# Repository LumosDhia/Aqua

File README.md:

# Aqua: smart farm water assistant

Hackathon project for Kizuna 2026 (21 to 22 November 2026, Esprit Bloc E, teams of 2 to 4, prizes 4000 / 2000 / 1000 TND). Theme: water, energy and food. Target users: Tunisian farmers.

Source material from the 20 November sessions:

- Ideas, software plan, roadmap, checklist, walkthrough website: `~/our idea/`
- Working scaffold (backend, frontend, firmware, compose): `~/our idea/project/`
- Desktop and Android wrappers: `~/our idea/app/`
- Hardware step by step PDF with wiring and ESP32 code: `~/smart-watering-guide.pdf`
- Hackathon site copy: `~/kizuna2026/`

## 1. What the project should be

A farm assistant that knows the soil, the weather and the crop, and decides when and how much to water.

Core logic (the heart of the demo):

| Situation | Action |
|---|---|
| Tank empty | Block the pump, raise an alarm |
| Soil dry and rain is forecast | Skip watering, count the water saved |
| Soil dry and no rain | Short pump dose |
| Soil very dry | Tiny emergency dose |

Feature groups, by priority:

- Must: soil and tank sensors with a live dashboard, rain-aware decision, crop dropdown (popular Tunisian crops) with per-crop water calculation, water saved counter.
- Should: water budget calculator (week, month, year, per source: SONEDE, well, rain tank), WhatsApp alerts, chatbot specialised in Tunisian farming (Derja, French, English, with voice), farm visualiser with coloured plots.
- Could: solar panel calculator, season changing UI (the interface changes with the season).
- Maybe: satellite NDVI map, heat and drought warning, planting advisor, pest and fertiliser calendar, leak detection, weekly PDF report, offline mode, cooperative multi-farm view.
- Later: neighbour water market (premium, needs a legal check, show as a mock screen).

Extra software adds that need no hardware: photo plant doctor, WhatsApp as the main interface, weekly smart schedule with a reason per decision, litres and dinars saved counter, simulation sliders, demo data generator.

Accessibility: the farmer can talk to the chatbot with voice.

## 2. Architecture and stack

| Layer | Choice |
|---|---|
| Frontend | React, Vite, TypeScript, Tailwind, Recharts, Leaflet, i18next with RTL |
| Backend | FastAPI (Python), SQLAlchemy |
| Database | PostgreSQL in Docker on the VPS (SQLite in dev) |
| Sensors | ESP32 posts over HTTP every 15 minutes |
| Live updates | WebSocket or SSE from FastAPI |
| Weather | Open-Meteo (free, no key) |
| Chatbot | Open model served on our GPU server (gpu.mavubo.com) through an OpenAI compatible API, with vision for the plant doctor |
| Voice | Whisper for speech to text |
| WhatsApp | Twilio sandbox for the demo, Meta Cloud API later |
| Deploy | Docker Compose on the VPS behind Nginx Proxy Manager with https |
| Auth | JWT |
| Apps | Electron (desktop), Capacitor (Android) |

Rules: the apps always talk to the API, never directly to the database. Do not use Next.js, Flutter or React Native.

Hardware (from the owned inventory): ESP32, capacitive soil moisture sensor V1.2, HC-SR04 ultrasonic sensor for tank level (ECHO through a divider of 2 x 1k ohm), water sensor module as rain detector, 5V relay, mini DC water pump with its own power supply, LEDs with 330 ohm resistors, buzzer. The Arduino Uno is not used because it has no Wi-Fi. Still needed: silicone tube, a tank, a breadboard and wires.

Repo layout:

```
backend/    FastAPI + SQLAlchemy + Alembic
frontend/   React + Vite
firmware/   ESP32 sketch
docker-compose.yml   api + postgres
```

## 3. Folders and how to run it

```
site/      product home page (static, open index.html)
backend/   FastAPI API with login and roles
web/       login page and dashboard (React, Vite, TypeScript, Tailwind, Lucide)
firmware/  ESP32 sketch
design/    reference images the pages follow
```

Run the dashboard locally:

```
cd backend && python3 -m venv .venv && .venv/bin/pip install -r requirements.txt
.venv/bin/python seed.py && .venv/bin/uvicorn app.main:app --port 8000
cd web && npm install && npm run dev        # http://127.0.0.1:5173
```

The dashboard draws the farm from the plots the farmer enters: each plot gets a share of the map proportional to its area, and plots with a warning (dry soil, low tank, waiting for rain) get a glowing marker and a note on the plot.

### AI models on the GPU server

All AI features (the chat advisor, reading CVs, reading farm drawings, the plant doctor) call a language model hosted on our GPU server, `gpu.mavubo.com`, through an OpenAI compatible API (`POST /v1/chat/completions` with a JSON schema for structured answers). The backend settings are:

```
LLM_API_URL=https://gpu.mavubo.com/v1
LLM_API_KEY=            # only if the server asks for a key
LLM_MODEL=qwen2.5vl:7b  # the model name exactly as the server lists it
```

Serve the models with Ollama (simplest) or vLLM. Models to download on the GPU server:

| Use | Model | Pull command (Ollama) | VRAM, about |
|---|---|---|---|
| Default: chat, CVs, drawings, plant photos (text and images) | Qwen2.5-VL 7B Instruct | `ollama pull qwen2.5vl:7b` | 8 GB |
| Better quality, same features, if the GPU has room | Qwen2.5-VL 32B Instruct | `ollama pull qwen2.5vl:32b` | 24 GB |
| Text only, small GPU | Llama 3.1 8B Instruct | `ollama pull llama3.1:8b` | 6 GB |
| Text only, stronger reasoning | Qwen2.5 14B Instruct | `ollama pull qwen2.5:14b` | 10 GB |
| Speech to text for voice messages | Whisper large-v3 | `ollama` does not run it, use `faster-whisper` | 4 GB |

If you use vLLM instead, start it with the Hugging Face name, for example `vllm serve Qwen/Qwen2.5-VL-7B-Instruct`, and put that same name in `LLM_MODEL`. The chat advisor needs a model that can follow a JSON schema; the photo and drawing features need one of the vision models. Without the server the chat shows "The AI helper is not switched on yet" and everything else keeps working. The advisor sees the farm's live plots, readings and forecast, and accepts photos, PDFs and text files (up to four files of 5 MB per message). A long answer can take about 20 seconds.

### Workers

The Workers icon (under the chat in the left rail) holds the farm's team and its tasks. Add a worker, then assign tasks from the Tasks tab or from the chat: ask the advisor to check what needs doing and it proposes tasks as cards, and you approve each one (or Send all). The advisor never creates tasks on its own, so a photo or file in the chat cannot assign work. Managers and owners add and remove workers, technicians and above assign tasks and mark them done, viewers only read.

## Water, weather, market and jobs

The left rail has these pages (full plan in `docs/ROADMAP-water-market.md`):

- **Water**: tabs My water (tanks, wells, boreholes, the public network, with levels and refill per day), Needs (how much water the crops and animals need, from the FAO-56 method with the forecast evapotranspiration, the soil type and the irrigation efficiency, for today, 7 days, 30 days and a year, against what the farm has, with a plain verdict such as "You will run short in about 3 days") and Animals (herds and their drinking water).
- **Weather**: current conditions, 48 hours, 7 days, farm alerts (heat, frost, wind, heavy rain). Data comes from Open-Meteo, which needs no key. Its free tier is for non-commercial use, so check their terms or buy their plan before Aqua is sold.
- **Water market**: farmers list surplus water with photos, price (fixed, free or to agree), pickup or delivery, location and dates. Other farmers browse by governorate, source, price and distance, and send an inquiry. Sellers read and answer inquiries in their inbox.
- **Jobs**: farmers post a one-off task, a job for a period or a long-term job; anyone with an account applies; the farm accepts or declines. A job fills when enough people are accepted.

### People: accounts, hiring and trust

Two kinds of people use Aqua. At sign-up you choose **farmer** or **farm worker**, and one person can switch sides later without losing anything.

- **Farmers** get a setup wizard (name and region, crops and sizes, water sources, animals, a written description or a hand-drawn picture), then a dashboard built from the answers.
- **Workers** get a Worker home (active work, applications, jobs near them, messages, profile checklist), a profile (headline, skills, languages, where they live, how far they will travel, public or private) and a CV that they can upload, fill in by hand or describe in words. Reading and writing CVs with AI needs the AI model server; without it the manual form still works.
- **Matching by distance**: workers see jobs within their own travel distance and within the reach the farm gave the job. Farmers see public workers who are looking for work within the radius they pick. Private profiles never appear and cannot apply.
- **Hiring**: accepting an application creates an engagement. The farmer marks it finished (it becomes confirmed work history on the worker's public profile), disapproves it with a reason, or offers full time after temporary work.
- **Chat**: after a hire, the farm and the worker talk in the Messages page, with unread counts. Email and phone are never shown.
- **Reports**: anyone can report a person (scam, no-show, unsafe, harassment, other), at most five a day. An admin reviews them, adds a note, resolves or dismisses, and can suspend an account, which locks it out at once and can be lifted.

CV files and farm drawings are private files, served only to their owner (and farm members for drawings). People and farms are placed by governorate, so distances are between governorate centres.

### Sample community

`backend/seed_market.py` creates eight fictional farmers (farms, water, listings with photos, job posts, inquiries and applications) so the market and jobs pages look real. Everyone shares the password in the script (`aqua-demo-2026`), for example `mohamed.karoui@aqua.test`. All people and businesses are invented. Photos are from Wikimedia Commons, credits in `backend/seed_media/CREDITS.md`.

```
cd backend
.venv/bin/python seed.py            # demo farm and the five role logins
.venv/bin/python seed_market.py     # sample community (add --reset to start over)
```

`backend/seed_people.py` adds eight fictional workers (profiles and CVs, one private, one not looking), three hires (active, finished, disapproved) with chats and two reports. It needs the two scripts above first, and `--reset` removes only the people it made.

```
.venv/bin/python seed_people.py     # sample workers, hires, chats and reports
```

Delete the demo accounts before any real use.

### Deploying these changes

- The API creates the new tables and adds the plot `soil_type` column by itself on start.
- Uploaded photos live in the `uploads` volume in `docker-compose.yml` (`UPLOADS_DIR=/data/uploads`) and are served at `/uploads`. Proxy `/uploads` to the API together with `/api`.
- The sample community is for demos only, do not run `seed_market.py` or `seed_people.py` on a real farm database.

## 3b. Older notes on running the scaffold

### Run locally

```
# backend, terminal 1
cd ~/our\ idea/project/backend
python3 -m venv .venv && .venv/bin/pip install -r requirements.txt
.venv/bin/python seed.py
.venv/bin/uvicorn app.main:app --reload        # http://localhost:8000/docs

# frontend, terminal 2
cd ~/our\ idea/project/frontend
npm install && npm run dev                     # http://localhost:5173
```

### Deploy on the VPS

```
cp .env.example .env        # set POSTGRES_PASSWORD and DEVICE_API_KEY
docker compose up -d --build
```

The API binds to 127.0.0.1:8000. Put it behind Nginx Proxy Manager with https, then set `CORS_ORIGINS` to the real origins: `http://localhost`, `https://localhost`, `capacitor://localhost`, and `null` for Electron.

### Desktop and Android apps

```
cd ~/our\ idea/project
./link-wrappers.sh https://api.yourdomain.com
cd ../app
npm run desktop           # Electron
npm run android:build     # APK, needs the Android SDK
```

Android SDK install was still downloading at the end of the 20 November session. Check `ANDROID_HOME` before building. iOS needs a Mac.

### Firmware

Open `firmware/` in the Arduino IDE, set Wi-Fi name and password, the API URL and `DEVICE_API_KEY`. Calibrate the soil and tank values yourself, the numbers in the sketch are guesses. Power the pump from its own supply, not USB.

### API

- `GET /health`
- `GET /api/crops`, `GET/POST /api/farms`, `POST /api/farms/{id}/plots`
- `POST /api/readings` (header `X-API-Key`), `GET /api/plots/{id}/readings`
- `POST /api/plots/{id}/decide`, `GET /api/plots/{id}/saved`

## 4. Plan for the 25 hours

1. Hours 0 to 3: agree scope, split roles, collect crop data (Kc, water needs).
2. Hours 3 to 10: ESP32 prototype and backend receiving data, dashboard skeleton in parallel.
3. Hours 10 to 16: decision engine with weather API, crop calculator, water saved counter.
4. Hours 16 to 20: chatbot with voice, WhatsApp alert, farm visualiser.
5. Hours 20 to 23: polish, season theme, mock screens for market and solar.
6. Hours 23 to 25: rehearse the pitch, record a backup demo video.

Roles: hardware and sensors, backend and decision engine, frontend and visualiser, chatbot and pitch.

## 5. Done and not done

Done: scaffold with farms, plots, readings, rain-aware decision with live Open-Meteo, saved counter, seed data, 3 passing tests, dashboard with chart, ESP32 sketch, Compose tested with Postgres, Electron tested, Capacitor Android platform added.

Also done: login (JWT) and role based access control (admin, owner, manager, technician, viewer), see `~/our idea/project/README.md`.

Not done: FAO water formula (placeholder of 4 L/m2 now), chatbot, WhatsApp, Leaflet map, i18n, Android SDK finish.

## 6. Pitch outline

1. Problem: summer 2026 was the hottest on record in Tunisia, power cuts stop pumps, farmers lose water.
2. Idea: an assistant that knows soil, weather and crop.
3. Live demo: dry soil, rain forecast, the system saves water and tells the farmer on WhatsApp.
4. Impact: litres and dinars saved.
5. Growth: neighbour water market and cooperatives.
6. Why us: Tunisia and Japan, two cultures that farm with scarce water.

Risks: water resale rules in Tunisia, WhatsApp API approval time, Derja speech to text quality, sensor calibration. Keep demo data ready in case a sensor dies live.

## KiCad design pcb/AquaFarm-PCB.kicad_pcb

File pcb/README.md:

# AquaFarm irrigation controller PCB

## Rebuild

Run from the project directory on Debian with KiCad 9.0.2, its standard libraries under `/usr/share/kicad`, and the Python interpreter that provides `pcbnew`.

```sh
/usr/bin/python3 -B build_sch.py
/usr/bin/python3 -B build_pcb.py
kicad-cli sch erc --exit-code-violations -o /tmp/aquafarm-erc.rpt AquaFarm-PCB.kicad_sch
kicad-cli pcb drc --exit-code-violations -o /tmp/aquafarm-drc.rpt AquaFarm-PCB.kicad_pcb
```

The builders overwrite `AquaFarm-PCB.kicad_sch`, `AquaFarm-PCB.kicad_pcb` and `BOM.csv`. `design.py` defines the parts, board placement and electrical assignments. A successful routing run should report `ROUTED 33/33 nets` and an empty routing unconnected list. The four `M3` BOM entries describe mounting locations. Order the screws and other hardware for the enclosure separately.

## Build assumptions

- Fabrication stack is 100 × 80 mm with R3 corners, two layers of 1 oz copper and 1.6 mm FR-4. The fabrication and placement-grid origins are at the lower-left corner of the nominal outline. Use a 1 mm placement grid. The ESP32 row pitch and the 3.5 mm mounting offsets use their specified dimensions.
- The socket is for the 30-pin DOIT DEVKIT V1, with 22.86 mm between rows. Fit the module with its antenna toward the top edge. Verify the antenna overhang and USB access with the actual module on a 1:1 print. The two-layer keepout covers the inboard antenna region between the sockets.
- J3 through J6 use keyed JST-XH housings at 2.50 mm pitch. Confirm the order printed on the GC9A01 against J7. The firmware assignments in the report assume CS on GPIO15 and DC on GPIO19. The `SDA` and `SCL` markings on the display connector carry SPI data and clock.
- F1 uses the indexed `Fuse:Fuse_BelFuse_0ZRE0016FF_L9.9mm_W3.8mm` footprint as the closest radial geometry. Specify a 1.5 A hold-current PTC for assembly and verify its staggered lead positions against the footprint, at `(0, 0)` and `(5.10, 1.60)` mm in library coordinates.
- D6 (1N5819) is a series Schottky diode that provides reverse-polarity protection for the board's `+5V` rail. The input at J1.1 connects to F1.1 on `+5V_IN`. The fuse output at F1.2 connects to D6.2 (anode) on `+5V_FUSED`, and D6.1 (cathode) feeds the board's `+5V` rail.
- The bottom-layer pump and relay returns join the logic return at J1.2. The gap in both ground pours preserves that junction. Use a C6 rated at least 10 V and confirm that the pump’s running and startup current fits the 5 V supply budget from the wiring report.

## K1 relay pad map

**Verify against relay datasheet** for the exact SRD-05VDC-SL-C part being fitted. The board uses the KiCad SANYOU SRD Form C pad numbering.

| K1 pad | Function | Board connection |
| --- | --- | --- |
| 1 | COM | +5V |
| 2 | Coil+ | +5V |
| 3 | NO | PUMP_SW |
| 4 | NC | Leave empty |
| 5 | Coil− | Q1_COLL |

## Connector pin map

Each row lists the pins starting at the marked pin 1.

| Ref | Connector | Pins in order |
| --- | --- | --- |
| J1 | 5 V input | +5V_IN, GND |
| J2 | Pump | PUMP_SW (pump+), GND (pump−) |
| J3 | Soil | +3V3, GND, AOUT |
| J4 | Rain | +3V3, GND, S (analog) |
| J5 | HC-SR04 | +5V, TRIG, ECHO (5 V), GND |
| J6 | DHT11 | +3V3, DATA, GND |
| J7 | Display | RST, CS, DC, SDA, SCL, GND, +3V3 |
| J8 | Spare | GPIO13, GPIO14, GPIO16, GPIO17, +3V3, GND |

### ESP32 sockets

Read both rows from the antenna end toward the bottom edge. NC denotes a deliberately open socket pad.

| Pad | J9 left pin | Board net | J10 right pin | Board net |
| --- | --- | --- | --- | --- |
| 1 | EN | NC | 3V3 | +3V3 |
| 2 | GPIO36 | NC | GND | GND |
| 3 | GPIO39 | NC | GPIO15 | LCD_CS |
| 4 | GPIO34 | SOIL_AOUT | GPIO2 | NC |
| 5 | GPIO35 | RAIN_A | GPIO4 | DHT_DATA |
| 6 | GPIO32 | LED_R | GPIO16 | SPARE_16 |
| 7 | GPIO33 | LED_B | GPIO17 | SPARE_17 |
| 8 | GPIO25 | LED_G | GPIO5 | LCD_SCL |
| 9 | GPIO26 | RELAY_DRV | GPIO18 | US_ECHO_3V3 |
| 10 | GPIO27 | US_TRIG | GPIO19 | LCD_DC |
| 11 | GPIO14 | SPARE_14 | GPIO21 | LCD_SDA |
| 12 | GPIO12 | NC | GPIO3/RX | NC |
| 13 | GPIO13 | SPARE_13 | GPIO1/TX | NC |
| 14 | GND | GND | GPIO22 | LCD_RST |
| 15 | VIN | +5V | GPIO23 | BUZZ_DRV |

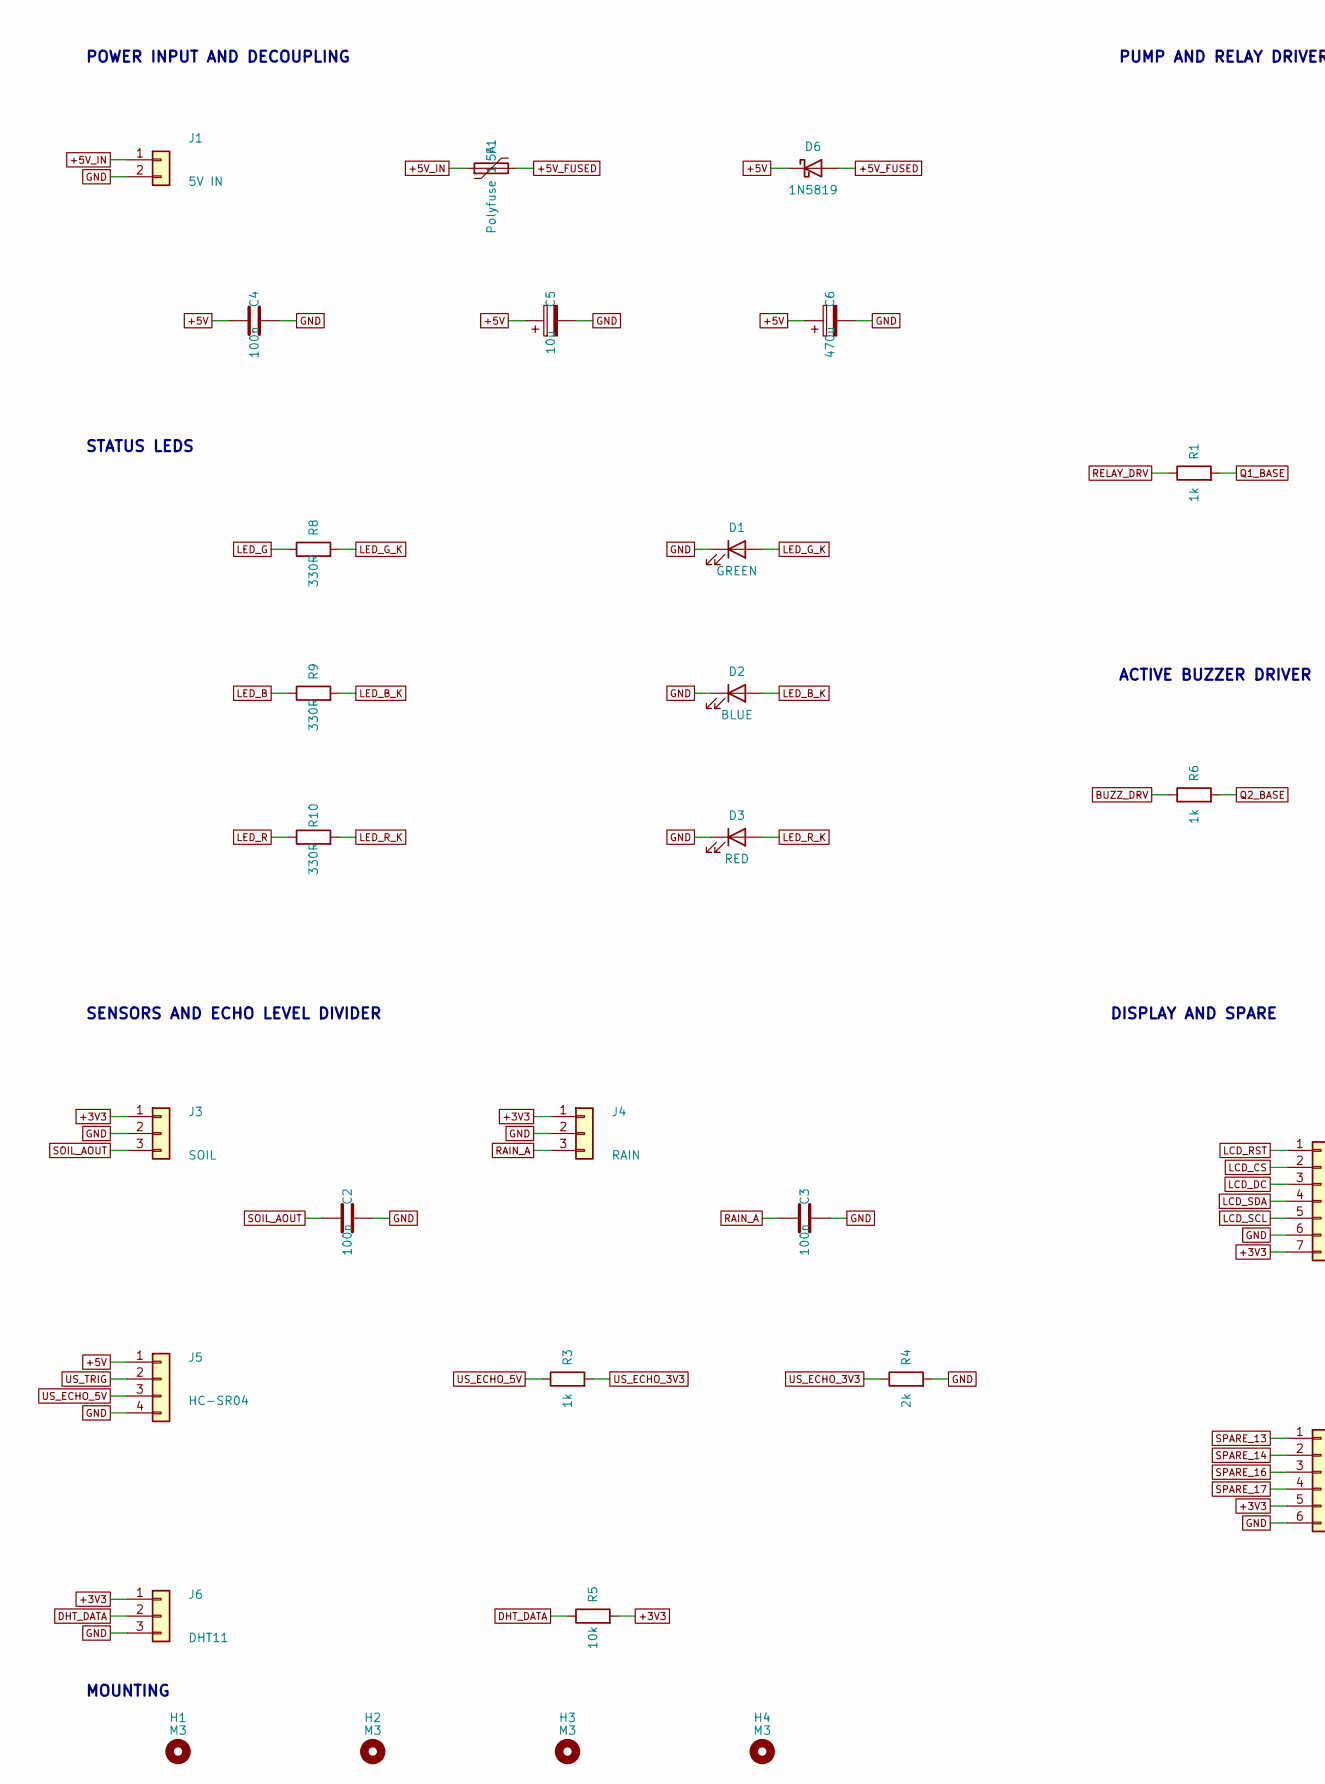
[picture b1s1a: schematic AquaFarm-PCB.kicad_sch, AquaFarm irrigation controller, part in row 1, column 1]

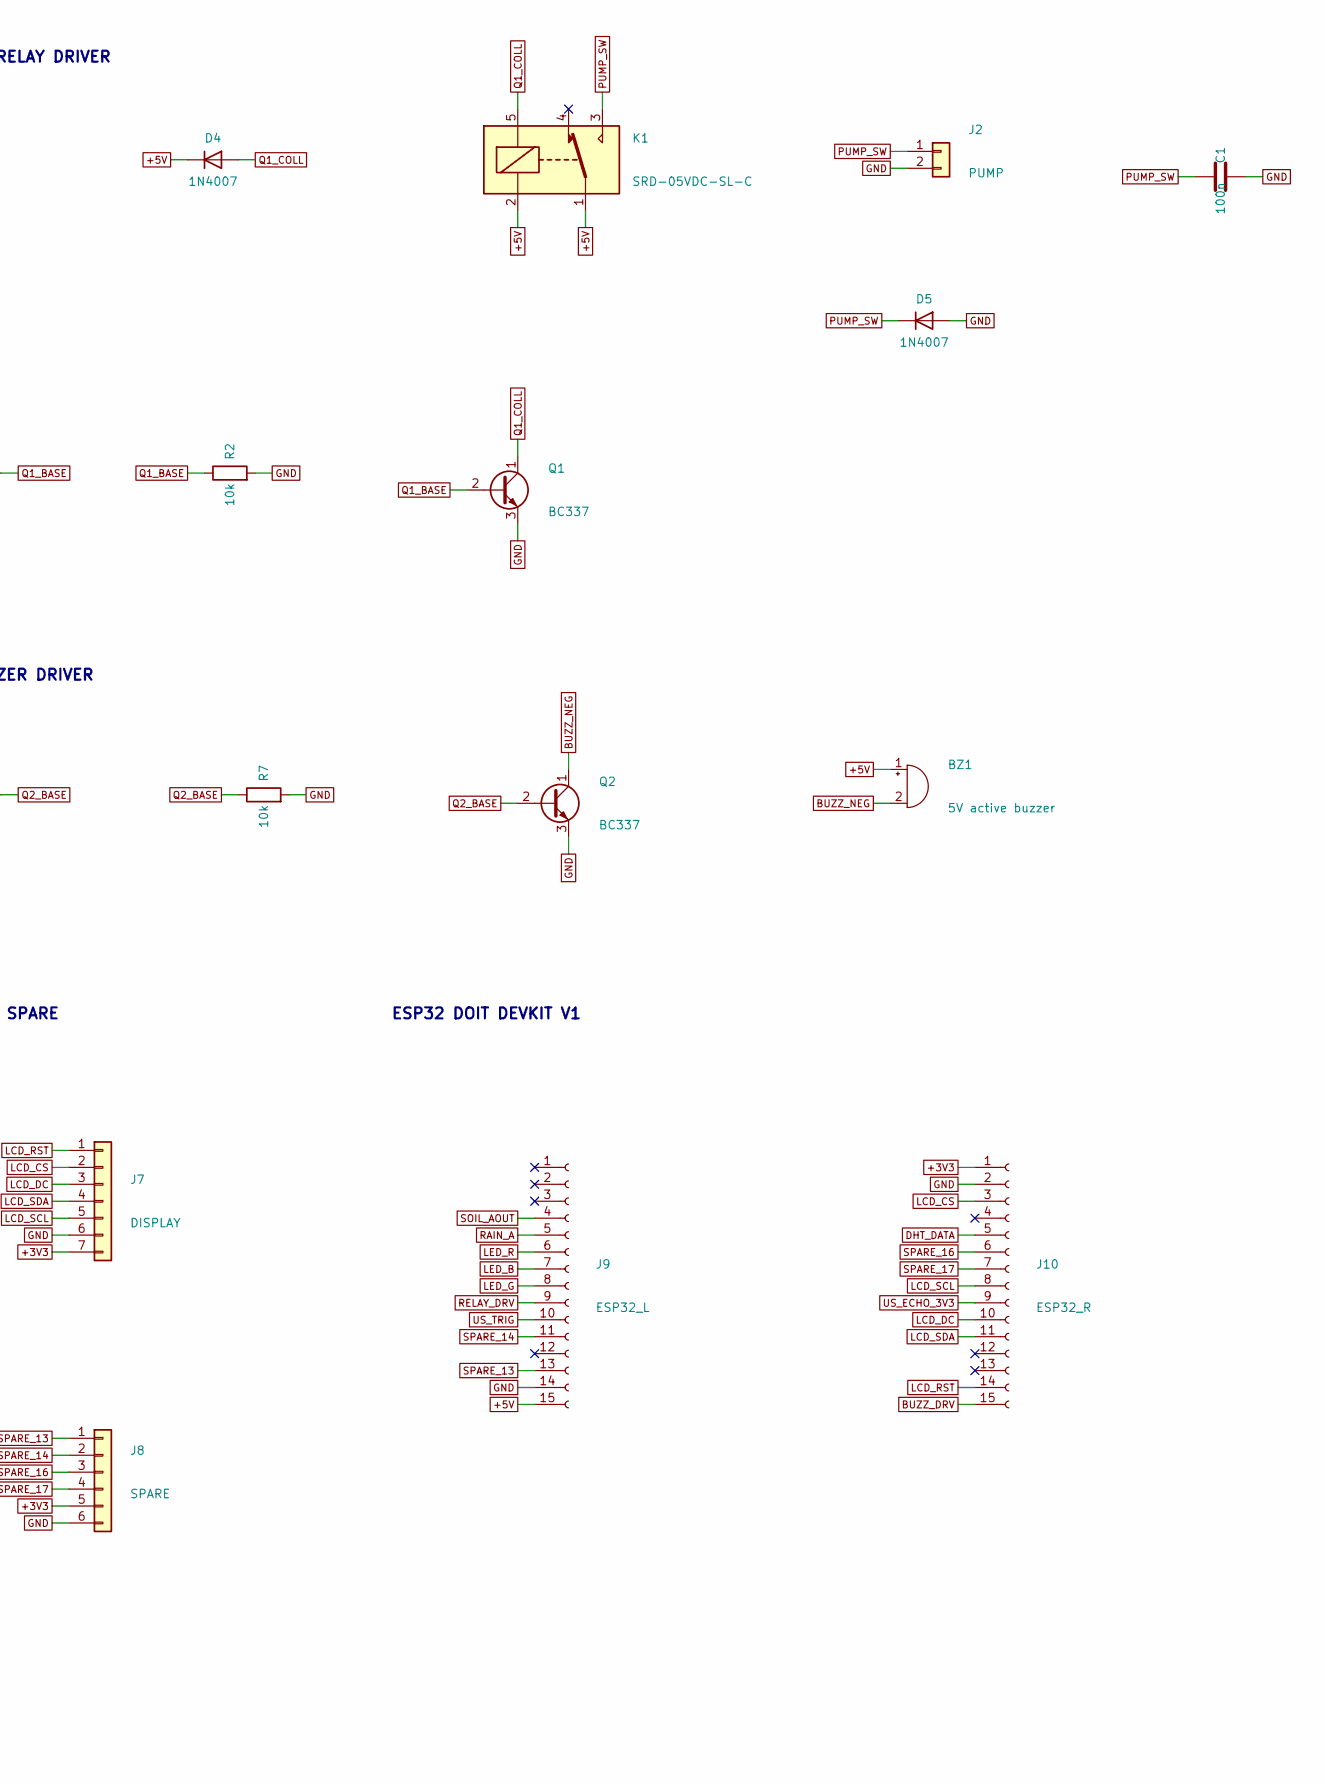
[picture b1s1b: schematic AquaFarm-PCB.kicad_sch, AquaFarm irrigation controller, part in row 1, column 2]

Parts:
BZ1: 5V active buzzer; Buzzer_12x9.5RM7.6
C1, C2, C3, C4: 100n; C_Disc_D5.0mm_W2.5mm_P5.00mm
C5: 10u; CP_Radial_D5.0mm_P2.00mm
C6: 470u; CP_Radial_D10.0mm_P5.00mm
D1: GREEN; LED_D5.0mm
D2: BLUE; LED_D5.0mm
D3: RED; LED_D5.0mm
D4, D5: 1N4007; D_DO-41_SOD81_P10.16mm_Horizontal
D6: 1N5819; D_DO-41_SOD81_P10.16mm_Horizontal
F1: Polyfuse 1.5A; Fuse_BelFuse_0ZRE0016FF_L9.9mm_W3.8mm
H1, H2, H3, H4: M3; MountingHole_3.2mm_M3
J1: 5V IN; TerminalBlock_bornier-2_P5.08mm
J2: PUMP; TerminalBlock_bornier-2_P5.08mm
J3: SOIL; JST_XH_B3B-XH-A_1x03_P2.50mm_Vertical
J4: RAIN; JST_XH_B3B-XH-A_1x03_P2.50mm_Vertical
J5: HC-SR04; JST_XH_B4B-XH-A_1x04_P2.50mm_Vertical
J6: DHT11; JST_XH_B3B-XH-A_1x03_P2.50mm_Vertical
J7: DISPLAY; PinHeader_1x07_P2.54mm_Vertical
J8: SPARE; PinHeader_1x06_P2.54mm_Vertical
J9: ESP32_L; PinSocket_1x15_P2.54mm_Vertical
J10: ESP32_R; PinSocket_1x15_P2.54mm_Vertical
K1: SRD-05VDC-SL-C; Relay_SPDT_SANYOU_SRD_Series_Form_C
Q1, Q2: BC337; TO-92_Inline
R1, R3, R6: 1k; R_Axial_DIN0207_L6.3mm_D2.5mm_P7.62mm_Horizontal
R2, R5, R7: 10k; R_Axial_DIN0207_L6.3mm_D2.5mm_P7.62mm_Horizontal
R4: 2k; R_Axial_DIN0207_L6.3mm_D2.5mm_P7.62mm_Horizontal
R8, R9, R10: 330R; R_Axial_DIN0207_L6.3mm_D2.5mm_P7.62mm_Horizontal

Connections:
+3V3: J3.1, J4.1, J6.1, J7.7, J8.5, J10.1, R5.2
+5V: BZ1.1 (+), C4.1, C5.1, C6.1, D4.1 (K), D6.1 (K), J5.1, J9.15, K1.1, K1.2
+5V_FUSED: D6.2 (A), F1.2
+5V_IN: F1.1, J1.1
BUZZ_DRV: J10.15, R6.1
BUZZ_NEG: BZ1.2 (-), Q2.1 (C)
DHT_DATA: J6.2, J10.5, R5.1
GND: C1.2, C2.2, C3.2, C4.2, C5.2, C6.2, D1.1 (K), D2.1 (K), D3.1 (K), D5.2 (A), J1.2, J2.2, J3.2, J4.2, J5.4, J6.3, J7.6, J8.6, J9.14, J10.2, Q1.3 (E), Q2.3 (E), R2.2, R4.2, R7.2
LCD_CS: J7.2, J10.3
LCD_DC: J7.3, J10.10
LCD_RST: J7.1, J10.14
LCD_SCL: J7.5, J10.8
LCD_SDA: J7.4, J10.11
LED_B: J9.7, R9.1
LED_B_K: D2.2 (A), R9.2
LED_G: J9.8, R8.1
LED_G_K: D1.2 (A), R8.2
LED_R: J9.6, R10.1
LED_R_K: D3.2 (A), R10.2
PUMP_SW: C1.1, D5.1 (K), J2.1, K1.3
Q1_BASE: Q1.2 (B), R1.2, R2.1
Q1_COLL: D4.2 (A), K1.5, Q1.1 (C)
Q2_BASE: Q2.2 (B), R6.2, R7.1
RAIN_A: C3.1, J4.3, J9.5
RELAY_DRV: J9.9, R1.1
SOIL_AOUT: C2.1, J3.3, J9.4
SPARE_13: J8.1, J9.13
SPARE_14: J8.2, J9.11
SPARE_16: J8.3, J10.6
SPARE_17: J8.4, J10.7
US_ECHO_3V3: J10.9, R3.2, R4.1
US_ECHO_5V: J5.3, R3.1
US_TRIG: J5.2, J9.10

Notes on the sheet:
POWER INPUT AND DECOUPLING
PUMP AND RELAY DRIVER
STATUS LEDS
ACTIVE BUZZER DRIVER
SENSORS AND ECHO LEVEL DIVIDER
DISPLAY AND SPARE
ESP32 DOIT DEVKIT V1
MOUNTING

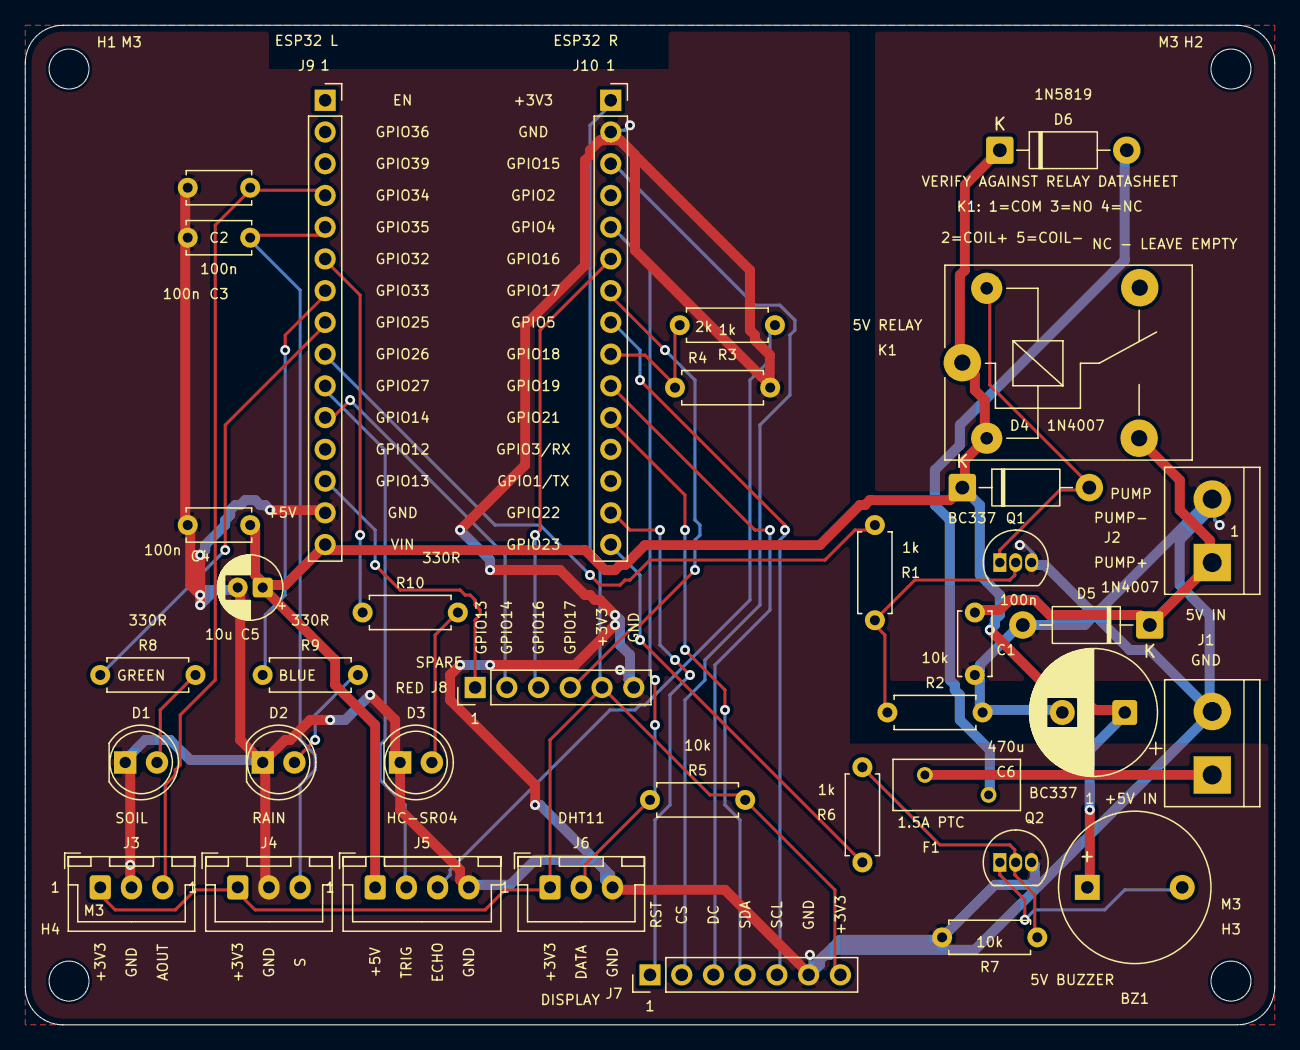
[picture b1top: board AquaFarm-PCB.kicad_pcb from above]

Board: 2 copper layers, 100.0 x 80.0 mm, 41 parts (0 on the bottom side), 33 nets.

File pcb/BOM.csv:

Reference,Quantity,Value,Footprint
J1,1,5V IN,TerminalBlock:TerminalBlock_bornier-2_P5.08mm
J2,1,PUMP,TerminalBlock:TerminalBlock_bornier-2_P5.08mm
J3,1,SOIL,Connector_JST:JST_XH_B3B-XH-A_1x03_P2.50mm_Vertical
J4,1,RAIN,Connector_JST:JST_XH_B3B-XH-A_1x03_P2.50mm_Vertical
J5,1,HC-SR04,Connector_JST:JST_XH_B4B-XH-A_1x04_P2.50mm_Vertical
J6,1,DHT11,Connector_JST:JST_XH_B3B-XH-A_1x03_P2.50mm_Vertical
J7,1,DISPLAY,Connector_PinHeader_2.54mm:PinHeader_1x07_P2.54mm_Vertical
J8,1,SPARE,Connector_PinHeader_2.54mm:PinHeader_1x06_P2.54mm_Vertical
J9,1,ESP32_L,Connector_PinSocket_2.54mm:PinSocket_1x15_P2.54mm_Vertical
J10,1,ESP32_R,Connector_PinSocket_2.54mm:PinSocket_1x15_P2.54mm_Vertical
K1,1,SRD-05VDC-SL-C,Relay_THT:Relay_SPDT_SANYOU_SRD_Series_Form_C
Q1,1,BC337,Package_TO_SOT_THT:TO-92_Inline
Q2,1,BC337,Package_TO_SOT_THT:TO-92_Inline
D1,1,GREEN,LED_THT:LED_D5.0mm
D2,1,BLUE,LED_THT:LED_D5.0mm
D3,1,RED,LED_THT:LED_D5.0mm
D4,1,1N4007,Diode_THT:D_DO-41_SOD81_P10.16mm_Horizontal
D5,1,1N4007,Diode_THT:D_DO-41_SOD81_P10.16mm_Horizontal
D6,1,1N5819,Diode_THT:D_DO-41_SOD81_P10.16mm_Horizontal
R1,1,1k,Resistor_THT:R_Axial_DIN0207_L6.3mm_D2.5mm_P7.62mm_Horizontal
R2,1,10k,Resistor_THT:R_Axial_DIN0207_L6.3mm_D2.5mm_P7.62mm_Horizontal
R3,1,1k,Resistor_THT:R_Axial_DIN0207_L6.3mm_D2.5mm_P7.62mm_Horizontal
R4,1,2k,Resistor_THT:R_Axial_DIN0207_L6.3mm_D2.5mm_P7.62mm_Horizontal
R5,1,10k,Resistor_THT:R_Axial_DIN0207_L6.3mm_D2.5mm_P7.62mm_Horizontal
R6,1,1k,Resistor_THT:R_Axial_DIN0207_L6.3mm_D2.5mm_P7.62mm_Horizontal
R7,1,10k,Resistor_THT:R_Axial_DIN0207_L6.3mm_D2.5mm_P7.62mm_Horizontal
R8,1,330R,Resistor_THT:R_Axial_DIN0207_L6.3mm_D2.5mm_P7.62mm_Horizontal
R9,1,330R,Resistor_THT:R_Axial_DIN0207_L6.3mm_D2.5mm_P7.62mm_Horizontal
R10,1,330R,Resistor_THT:R_Axial_DIN0207_L6.3mm_D2.5mm_P7.62mm_Horizontal
C1,1,100n,Capacitor_THT:C_Disc_D5.0mm_W2.5mm_P5.00mm
C2,1,100n,Capacitor_THT:C_Disc_D5.0mm_W2.5mm_P5.00mm
C3,1,100n,Capacitor_THT:C_Disc_D5.0mm_W2.5mm_P5.00mm
C4,1,100n,Capacitor_THT:C_Disc_D5.0mm_W2.5mm_P5.00mm
C5,1,10u,Capacitor_THT:CP_Radial_D5.0mm_P2.00mm
C6,1,470u,Capacitor_THT:CP_Radial_D10.0mm_P5.00mm
BZ1,1,5V active buzzer,Buzzer_Beeper:Buzzer_12x9.5RM7.6
F1,1,Polyfuse 1.5A,Fuse:Fuse_BelFuse_0ZRE0016FF_L9.9mm_W3.8mm
H1,1,M3,MountingHole:MountingHole_3.2mm_M3
H2,1,M3,MountingHole:MountingHole_3.2mm_M3
H3,1,M3,MountingHole:MountingHole_3.2mm_M3
H4,1,M3,MountingHole:MountingHole_3.2mm_M3

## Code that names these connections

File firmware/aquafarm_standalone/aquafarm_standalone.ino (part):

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// ----------------------------

const int SOIL = 34, RAIN = 35, TRIG = 27, ECHO = 18;
const int RELAY = 26, LED_G = 25, LED_B = 33, LED_R = 32, BUZ = 23;
const int DHT_PIN = 4;

DHT dht(DHT_PIN, DHT11);
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  relay(false);                                            // pump OFF first, before anything else
  Serial.begin(115200);
  pinMode(TRIG, OUTPUT); pinMode(ECHO, INPUT);
  pinMode(LED_G, OUTPUT); pinMode(LED_B, OUTPUT); pinMode(LED_R, OUTPUT); pinMode(BUZ, OUTPUT);
  digitalWrite(BUZ, LOW);
  leds(false, false, false);
  dht.begin();
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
